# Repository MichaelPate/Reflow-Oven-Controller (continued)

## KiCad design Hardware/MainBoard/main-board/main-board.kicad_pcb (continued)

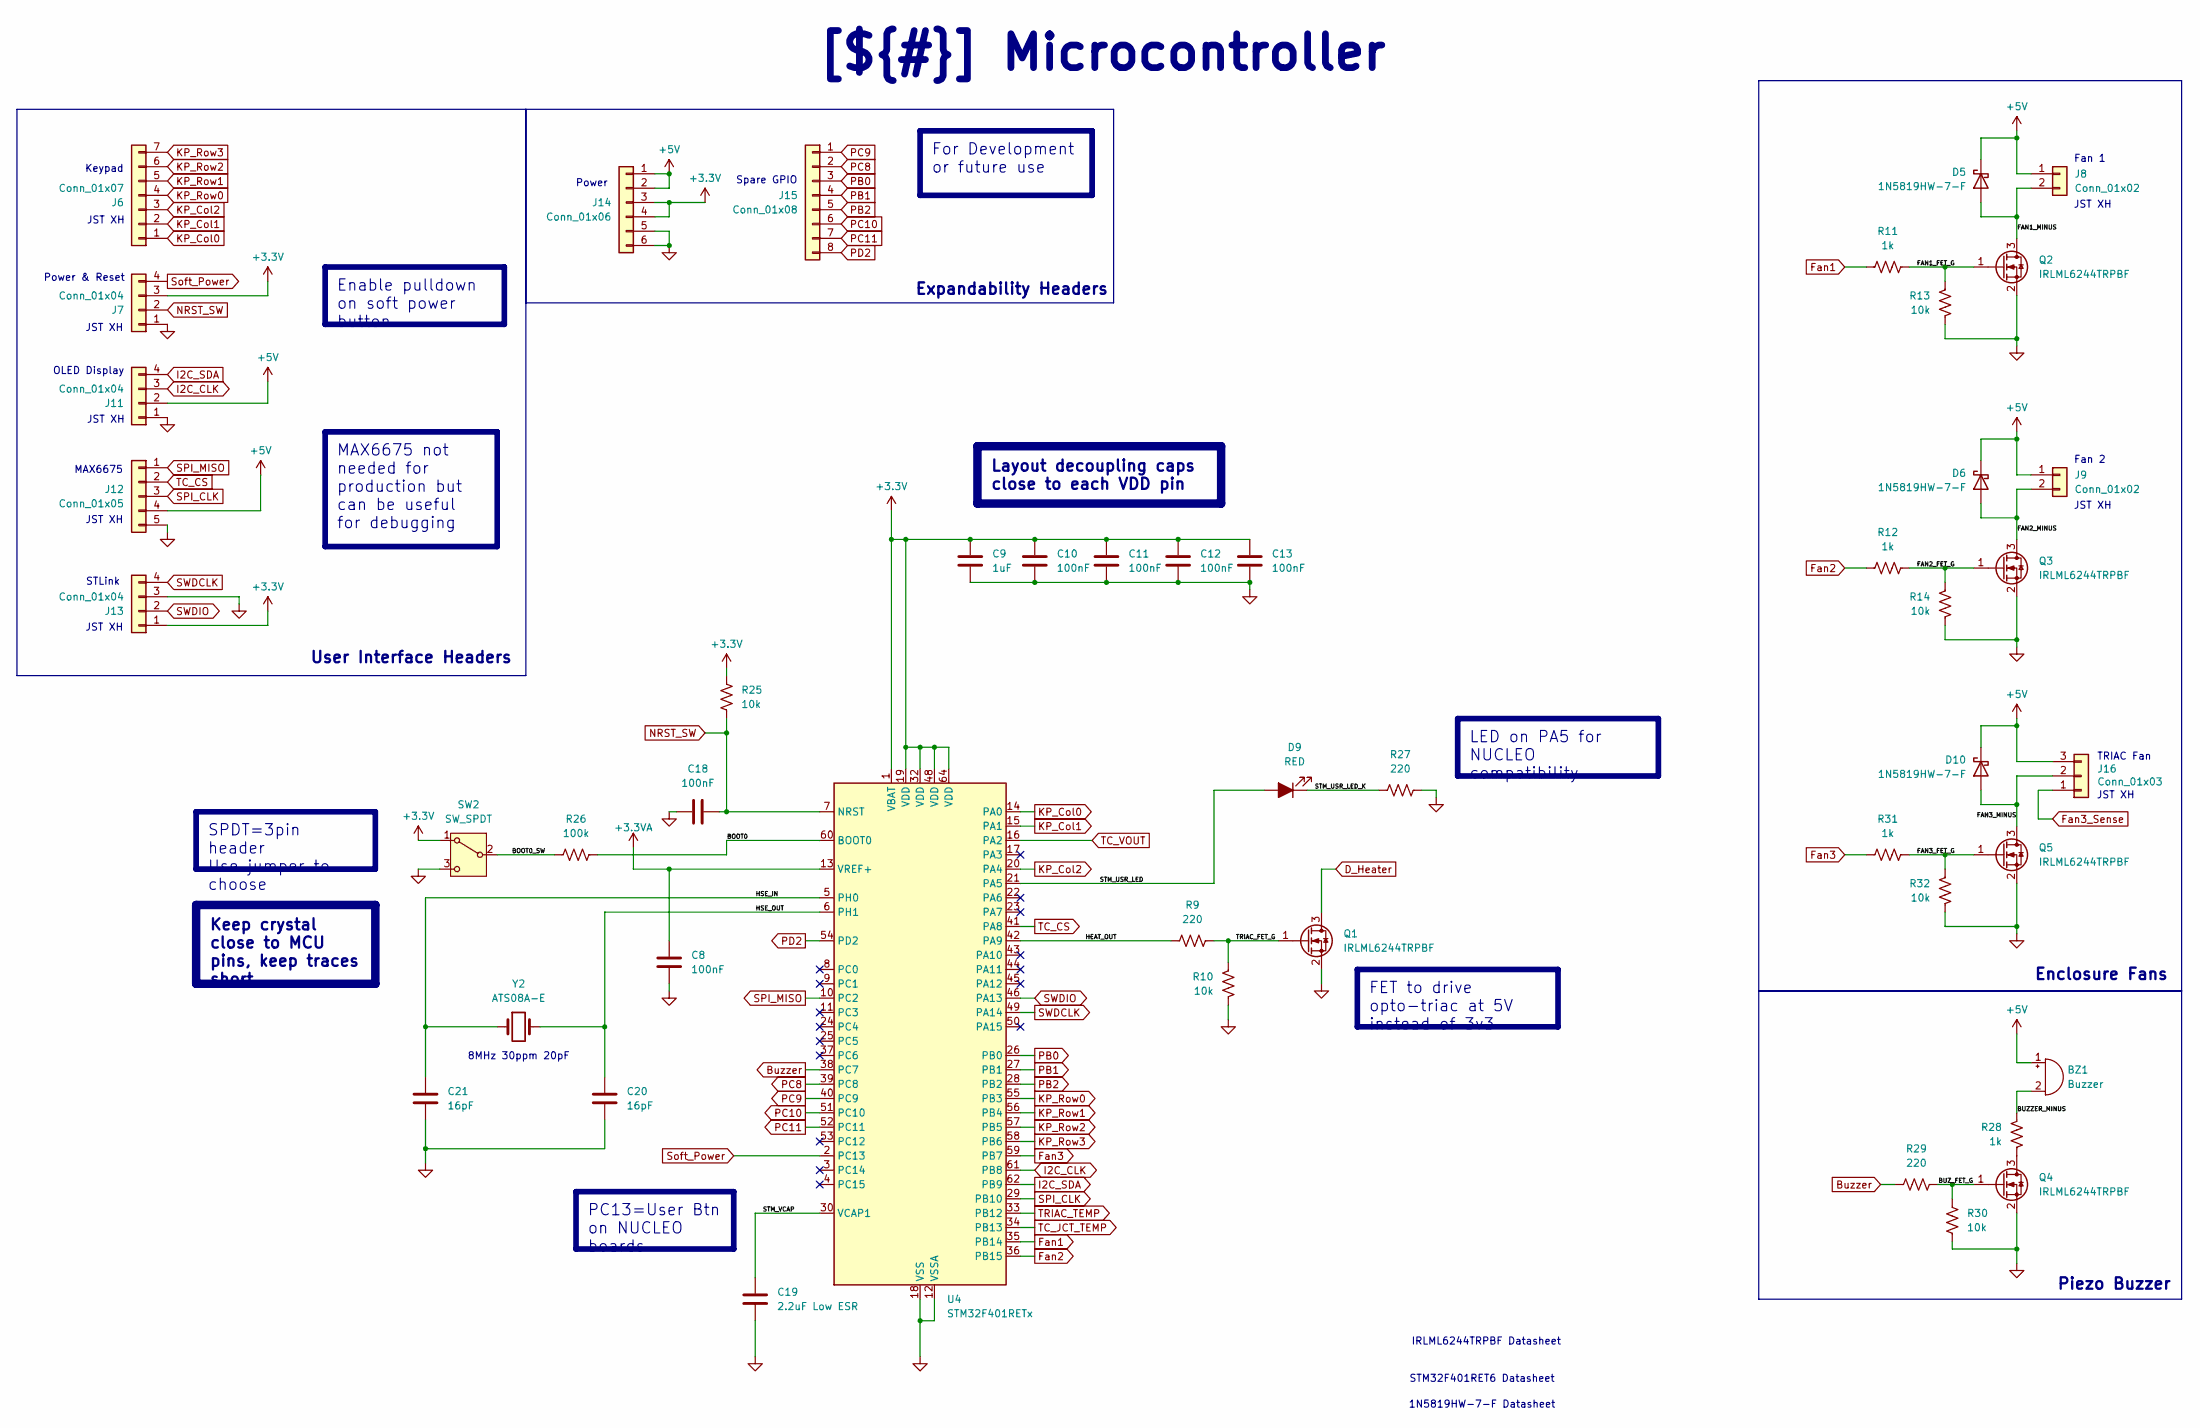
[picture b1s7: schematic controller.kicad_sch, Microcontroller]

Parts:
BZ1: Buzzer; Buzzer_12x9.5RM7.6
C8, C10, C11, C12, C13, C18: 100nF; C_0603_1608Metric_Pad1.08x0.95mm_HandSolder
C9: 1uF; C_0805_2012Metric_Pad1.18x1.45mm_HandSolder
C19: 2.2uF Low ESR; C_0805_2012Metric_Pad1.18x1.45mm_HandSolder
C20, C21: 16pF; C_0402_1005Metric_Pad0.74x0.62mm_HandSolder
D5, D6, D10: 1N5819HW-7-F; D_SOD-123
D9: RED; LED_0603_1608Metric_Pad1.05x0.95mm_HandSolder
J6: Conn_01x07; JST_XH_B7B-XH-A_1x07_P2.50mm_Vertical
J7, J11, J13: Conn_01x04; JST_XH_B4B-XH-A_1x04_P2.50mm_Vertical
J8, J9: Conn_01x02; JST_XH_B2B-XH-A_1x02_P2.50mm_Vertical
J12: Conn_01x05; JST_XH_B5B-XH-A_1x05_P2.50mm_Vertical
J14: Conn_01x06; PinHeader_1x06_P2.54mm_Vertical
J15: Conn_01x08; PinHeader_1x08_P2.54mm_Vertical
J16: Conn_01x03; JST_XH_B3B-XH-A_1x03_P2.50mm_Vertical
Q1, Q2, Q3, Q4, Q5: IRLML6244TRPBF; SOT-23
R9, R27, R29: 220; R_0603_1608Metric_Pad0.98x0.95mm_HandSolder
R10, R13, R14, R25, R30, R32: 10k; R_0603_1608Metric_Pad0.98x0.95mm_HandSolder
R11, R12, R28, R31: 1k; R_0603_1608Metric_Pad0.98x0.95mm_HandSolder
R26: 100k; R_0603_1608Metric_Pad0.98x0.95mm_HandSolder
SW2: SW_SPDT; PinHeader_1x03_P2.54mm_Vertical
U4: STM32F401RETx; LQFP-64_10x10mm_P0.5mm
Y2: ATS08A-E; Crystal_HC49-4H_Vertical

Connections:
+3.3V: C9.1, C10.1, C11.1, C12.1, C13.1, J7.3, J13.1, J14.3, J14.4, R25.1, SW2.1 (A), U4.1 (VBAT), U4.19 (VDD), U4.32 (VDD), U4.48 (VDD), U4.64 (VDD); also elsewhere on the board
+3.3VA: C8.1, U4.13 (VREF+); also elsewhere on the board
+5V: BZ1.1 (+), D5.1 (K), D6.1 (K), D10.1 (K), J8.1, J9.1, J11.2, J12.4, J14.1, J14.2, J16.3; also elsewhere on the board
/Block Diagram/MCU Page 5/BOOT0: R26.2, U4.60 (BOOT0)
/Block Diagram/MCU Page 5/BOOT0_SW: R26.1, SW2.2 (B)
/Block Diagram/MCU Page 5/BUZZER_MINUS: BZ1.2 (-), R28.1
/Block Diagram/MCU Page 5/BUZ_FET_G: Q4.1 (G), R29.2, R30.1
/Block Diagram/MCU Page 5/FAN1_FET_G: Q2.1 (G), R11.2, R13.1
/Block Diagram/MCU Page 5/FAN1_MINUS: D5.2 (A), J8.2, Q2.3 (D)
/Block Diagram/MCU Page 5/FAN2_FET_G: Q3.1 (G), R12.2, R14.1
/Block Diagram/MCU Page 5/FAN2_MINUS: D6.2 (A), J9.2, Q3.3 (D)
/Block Diagram/MCU Page 5/FAN3_FET_G: Q5.1 (G), R31.2, R32.1
/Block Diagram/MCU Page 5/FAN3_MINUS: D10.2 (A), J16.2, Q5.3 (D)
/Block Diagram/MCU Page 5/HEAT_OUT: R9.1, U4.42 (PA9)
/Block Diagram/MCU Page 5/HSE_IN: C21.1, U4.5 (PH0), Y2.1
/Block Diagram/MCU Page 5/HSE_OUT: C20.1, U4.6 (PH1), Y2.2
/Block Diagram/MCU Page 5/STM_USR_LED: D9.2 (A), U4.21 (PA5)
/Block Diagram/MCU Page 5/STM_USR_LED_K: D9.1 (K), R27.1
/Block Diagram/MCU Page 5/STM_VCAP: C19.1, U4.30 (VCAP1)
/Block Diagram/MCU Page 5/TRIAC_FET_G: Q1.1 (G), R9.2, R10.1
Buzzer: R29.1, U4.38 (PC7)
D_Heater: Q1.3 (D); also elsewhere on the board
Fan1: R11.1, U4.35 (PB14)
Fan2: R12.1, U4.36 (PB15)
Fan3: R31.1, U4.59 (PB7)
Fan3_Sense: J16.1
GND: C8.2, C9.2, C10.2, C11.2, C12.2, C13.2, C18.1, C19.2, C20.2, C21.2, J7.1, J11.1, J12.5, J13.3, J14.5, J14.6, Q1.2 (S), Q2.2 (S), Q3.2 (S), Q4.2 (S), Q5.2 (S), R10.2, R13.2, R14.2, R27.2, R30.2, R32.2, SW2.3 (C), U4.12 (VSSA), U4.18 (VSS), U4.31 (VSS), U4.47 (VSS), U4.63 (VSS); also elsewhere on the board
I2C_CLK: J11.3, U4.61 (PB8)
I2C_SDA: J11.4, U4.62 (PB9)
KP_Col0: J6.1, U4.14 (PA0)
KP_Col1: J6.2, U4.15 (PA1)
KP_Col2: J6.3, U4.20 (PA4)
KP_Row0: J6.4, U4.55 (PB3)
KP_Row1: J6.5, U4.56 (PB4)
KP_Row2: J6.6, U4.57 (PB5)
KP_Row3: J6.7, U4.58 (PB6)
NRST_SW: C18.2, J7.2, R25.2, U4.7 (NRST)
unnamed: Q4.3 (D), R28.2
PB0: J15.3, U4.26 (PB0)
PB1: J15.4, U4.27 (PB1)
PB2: J15.5, U4.28 (PB2)
PC8: J15.2, U4.39 (PC8)
PC9: J15.1, U4.40 (PC9)
PC10: J15.6, U4.51 (PC10)
PC11: J15.7, U4.52 (PC11)
PD2: J15.8, U4.54 (PD2)
SPI_CLK: J12.3, U4.29 (PB10)
SPI_MISO: J12.1, U4.10 (PC2)
SWDCLK: J13.4, U4.49 (PA14)
SWDIO: J13.2, U4.46 (PA13)
Soft_Power: J7.4, U4.2 (PC13)
TC_CS: J12.2, U4.41 (PA8)
TC_JCT_TEMP: U4.34 (PB13); also elsewhere on the board
TC_VOUT: U4.16 (PA2); also elsewhere on the board
TRIAC_TEMP: U4.33 (PB12); also elsewhere on the board

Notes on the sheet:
User Interface Headers
Piezo Buzzer
Enclosure Fans
Keypad
JST XH
8MHz 30ppm 20pF
Spare GPIO
TRIAC Fan
STM32F401RET6 Datasheet
1N5819HW-7-F Datasheet
MAX6675
Expandability Headers
Fan 1
Power
Power & Reset
OLED Display
STLink
IRLML6244TRPBF Datasheet
Fan 2
SPDT=3pin header Use jumper to choose
LED on PA5 for NUCLEO compatibility
MAX6675 not needed for production but can be useful for debugging
PC13=User Btn on NUCLEO boards
[${#}] ${TITLE}
Layout decoupling caps close to each VDD pin
For Development or future use
Keep crystal close to MCU pins, keep traces short
Enable pulldown on soft power button
FET to drive opto-triac at 5V instead of 3v3

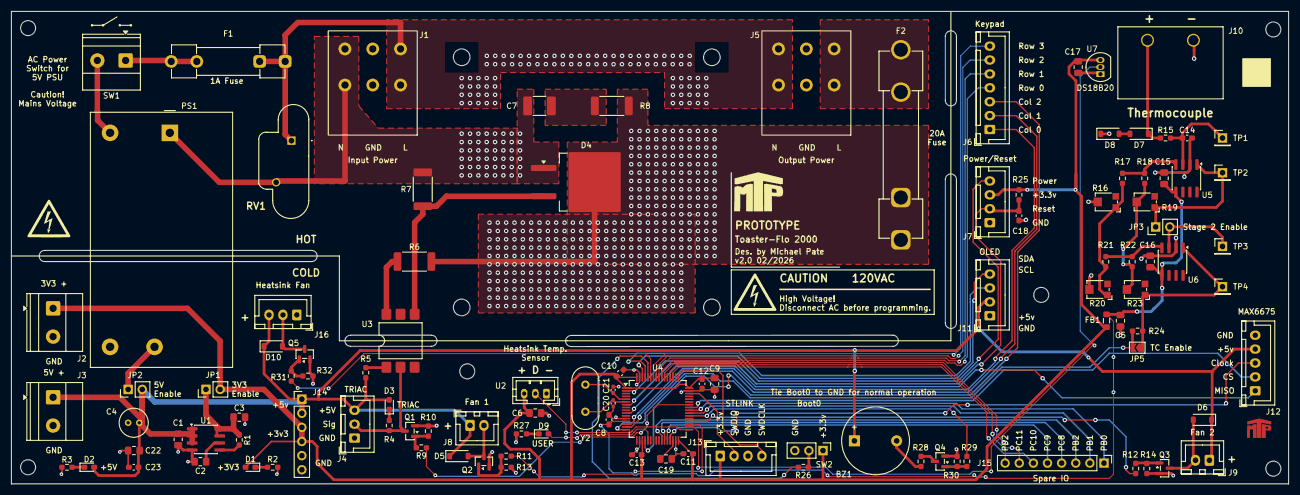
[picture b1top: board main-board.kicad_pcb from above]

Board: 4 copper layers, 229.8 x 85.0 mm, 122 parts (0 on the bottom side), 84 nets.

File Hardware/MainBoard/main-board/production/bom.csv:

Designator,Footprint,Quantity,Value,LCSC Part #
BZ1,Buzzer_12x9.5RM7.6,1,Buzzer,
"C1, C3, C5",0805,3,10uF,
"C10, C11, C12, C13, C18, C23, C8",0603,7,100nF,
C14,0603,1,104,
"C15, C16",0805,2,100nF,
"C17, C2, C22, C6, C9",0805,5,1uF,
C19,0805,1,2.2uF Low ESR,
"C20, C21",0402,2,16pF,
C4,C_Radial_D5.0mm_H5.0mm_P2.00mm,1,47uF,
C7,1812,1,10nF 250V,
"D1, D2, D3, D9",0603,4,RED,
"D10, D5, D6",D_SOD-123,3,1N5819HW-7-F,
D4,TO-263-2,1,T2035T-8G-RT,
"D7, D8",D_SOD-123,2,BZT52C4V7-13-F,
F1,Fuseholder_Clip-5x20mm_Littelfuse_100_Inline_P20.50x4.60mm_D1.30mm_Horizontal,1,1A,
F2,Fuseholder_Clip-6.3x32mm_Littelfuse_122_Inline_P34.21x7.62mm_D2.54mm_Horizontal,1,20A,
FB1,0805,1,WLBD2012HCU601TH,
"J1, J5",SPTA-THR 2.53-5.0 P26,2,1366005,
J10,CONN_4DB-P108-02_TEC,1,4DB-P108-02,
"J11, J13, J7",JST_XH_B4B-XH-A_1x04_P2.50mm_Vertical,3,Conn_01x04,
J12,JST_XH_B5B-XH-A_1x05_P2.50mm_Vertical,1,Conn_01x05,
J14,PinHeader_1x06_P2.54mm_Vertical,1,Conn_01x06,
J15,PinHeader_1x08_P2.54mm_Vertical,1,Conn_01x08,
"J16, J4",JST_XH_B3B-XH-A_1x03_P2.50mm_Vertical,2,Conn_01x03,
"J2, J3","TerminalBlock_Phoenix_MKDS-1,5-2-5.08_1x02_P5.08mm_Horizontal",2,Conn_01x02,
J6,JST_XH_B7B-XH-A_1x07_P2.50mm_Vertical,1,Conn_01x07,
"J8, J9",JST_XH_B2B-XH-A_1x02_P2.50mm_Vertical,2,Conn_01x02,
"JP1, JP2, JP3",PinHeader_1x02_P2.54mm_Vertical,3,Jumper_2_Open,
JP5,SolderJumper-2_P1.3mm_Open_TrianglePad1.0x1.5mm,1,Jumper_2_Open,
PS1,Converter_ACDC_MeanWell_IRM-10-xx_THT,1,IRM-10-5,
"Q1, Q2, Q3, Q4, Q5",SOT-23,5,IRLML6244TRPBF,
"R1, R10, R13, R14, R25, R30, R32",0603,7,10k,
"R11, R12, R15, R24, R28, R31",0603,6,1k,
"R16, R20",Potentiometer_Bourns_TC33X_Vertical,2,TC33X-2-103E,
"R17, R21",0603,2,15k,
"R18, R22",0603,2,560,
"R19, R23",Potentiometer_Bourns_TC33X_Vertical,2,TC33X-2-102E,
"R2, R27, R29, R9",0603,4,220,
R26,0603,1,100k,
"R3, R4, R5",0603,3,330,
"R6, R7",2512,2,330,
R8,2512,1,39,
RV1,TMOV20RP150E,1,TMOV20RP150E,
SW1,"TerminalBlock_Phoenix_MKDS-1,5-2-5.08_1x02_P5.08mm_Horizontal",1,SW_SPST,
SW2,PinHeader_1x03_P2.54mm_Vertical,1,SW_SPDT,
"TP1, TP2, TP3, TP4",PinHeader_1x01_P2.54mm_Vertical,4,TestPoint,
U1,SOIC-8_3.9x4.9mm_P1.27mm,1,MCP1727T-3302E/SN,
U2,JST_PH_B3B-PH-K_1x03_P2.00mm_Vertical,1,DS18B20+,
U3,SMDIP-6_W9.53mm,1,MOC3083S-TA1,
U4,LQFP-64_10x10mm_P0.5mm,1,STM32F401RETx,
"U5, U6",SOIC-8_3.9x4.9mm_P1.27mm,2,OPA333AIDCKT,
U7,TO-92_Inline,1,DS18B20+,
Y2,Crystal_HC49-4H_Vertical,1,ATS08A-E,

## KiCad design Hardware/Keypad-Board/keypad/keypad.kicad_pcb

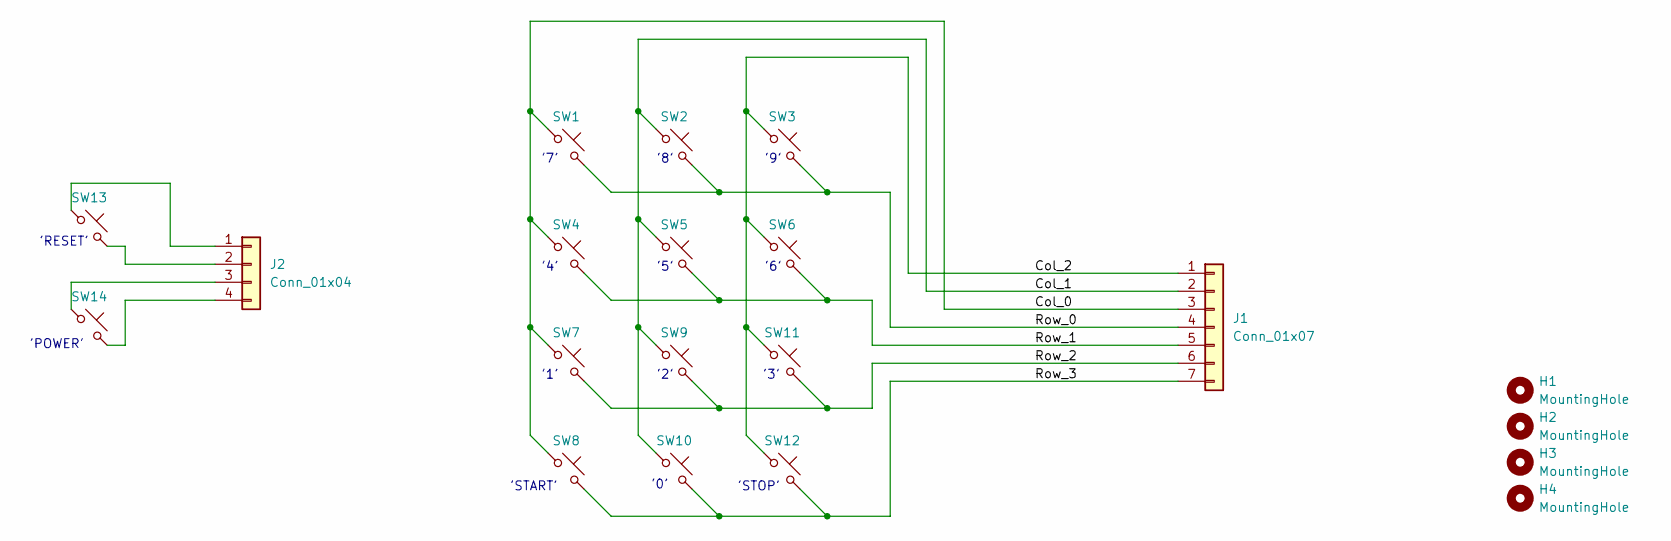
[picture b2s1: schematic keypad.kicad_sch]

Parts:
H1, H2, H3, H4: MountingHole; MountingHole_2.7mm_M2.5
J1: Conn_01x07; JST_XH_B7B-XH-A_1x07_P2.50mm_Vertical
J2: Conn_01x04; JST_XH_B4B-XH-A_1x04_P2.50mm_Vertical
SW1, SW2, SW3, SW4, SW5, SW6, SW7, SW8, SW9, SW10, SW11, SW12, SW13, SW14: SW_Push_45deg; SW_Cherry_MX_1.00u_PCB

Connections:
/Col_0: J1.3, SW1.1, SW4.1, SW7.1, SW8.1
/Col_1: J1.2, SW2.1, SW5.1, SW9.1, SW10.1
/Col_2: J1.1, SW3.1, SW6.1, SW11.1, SW12.1
/Row_0: J1.4, SW1.2, SW2.2, SW3.2
/Row_1: J1.5, SW4.2, SW5.2, SW6.2
/Row_2: J1.6, SW7.2, SW9.2, SW11.2
/Row_3: J1.7, SW8.2, SW10.2, SW12.2
unnamed: J2.1, SW13.1
unnamed: J2.2, SW13.2
unnamed: J2.3, SW14.1
unnamed: J2.4, SW14.2

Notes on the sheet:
'7'
'5'
'0'
'START'
'6'
'2'
'4'
'3'
'9'
'1'
'RESET'
'8'
'POWER'
'STOP'

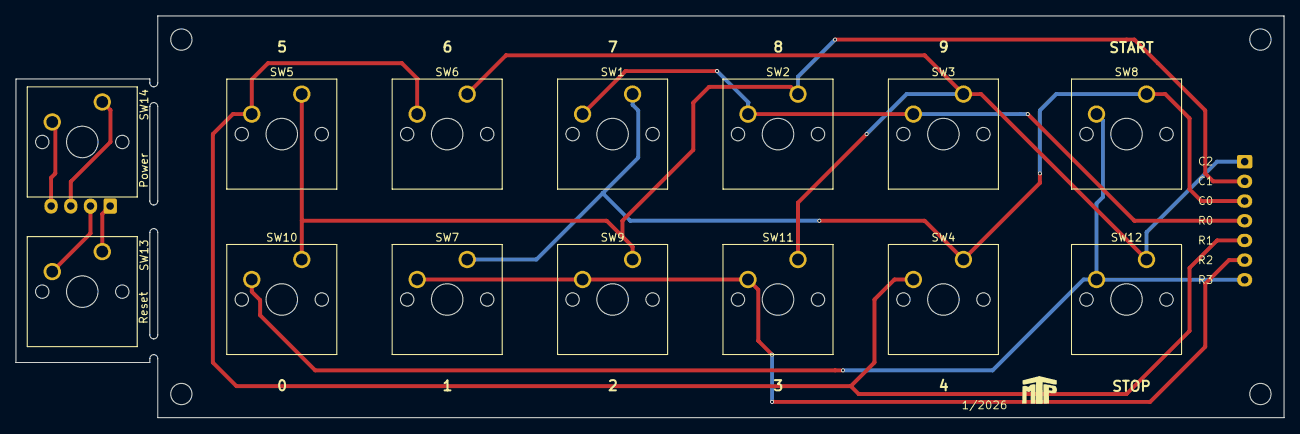
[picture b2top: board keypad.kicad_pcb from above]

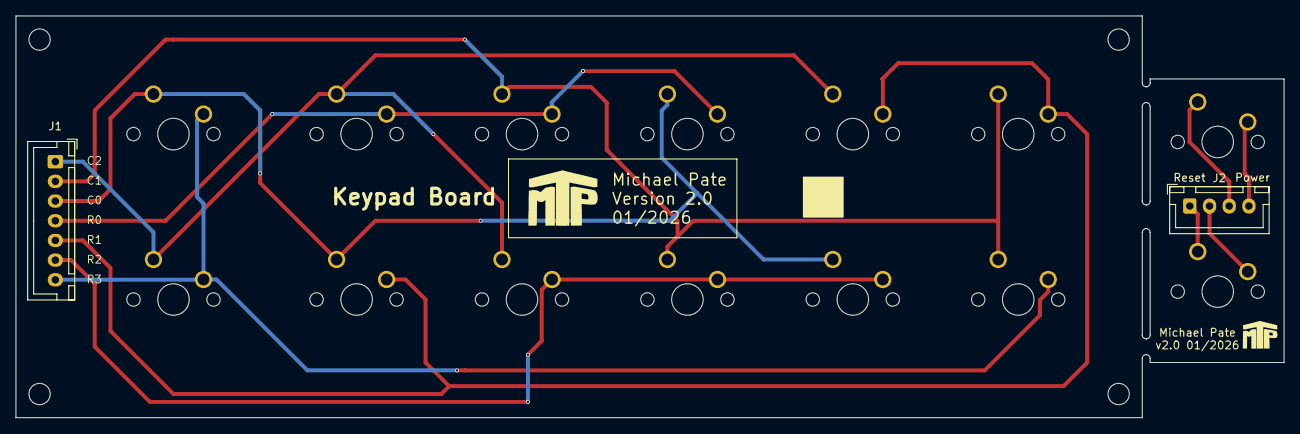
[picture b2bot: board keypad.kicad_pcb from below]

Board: 2 copper layers, 161.0 x 51.0 mm, 20 parts (2 on the bottom side), 11 nets.

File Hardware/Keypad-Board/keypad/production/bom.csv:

Designator,Footprint,Quantity,Value,LCSC Part #
J1,JST_XH_B7B-XH-A_1x07_P2.50mm_Vertical,1,Conn_01x07,
J2,JST_XH_B4B-XH-A_1x04_P2.50mm_Vertical,1,Conn_01x04,
"SW1, SW10, SW11, SW12, SW13, SW14, SW2, SW3, SW4, SW5, SW6, SW7, SW8, SW9",SW_Cherry_MX_1.00u_PCB,14,SW_Push_45deg,

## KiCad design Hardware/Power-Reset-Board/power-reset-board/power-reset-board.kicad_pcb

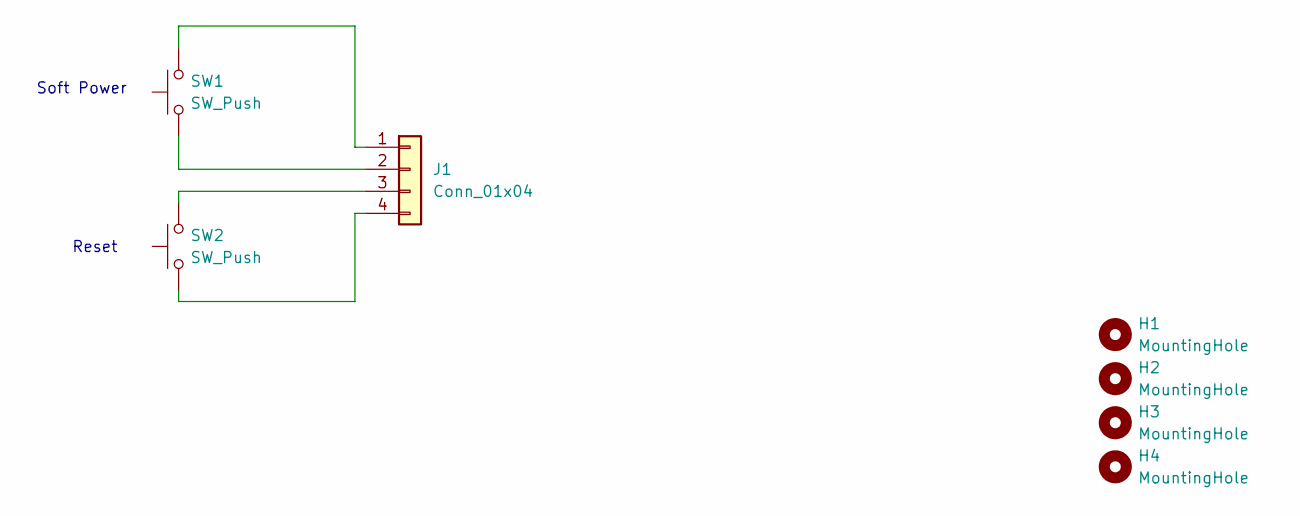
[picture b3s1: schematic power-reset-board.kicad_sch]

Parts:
H1, H2, H3, H4: MountingHole; MountingHole_2.7mm_M2.5
J1: Conn_01x04; JST_XH_B4B-XH-A_1x04_P2.50mm_Vertical
SW1, SW2: SW_Push; SW_Cherry_MX_1.00u_PCB

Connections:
unnamed: J1.1, SW1.2
unnamed: J1.2, SW1.1
unnamed: J1.3, SW2.2
unnamed: J1.4, SW2.1

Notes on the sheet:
Soft Power
Reset

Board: 2 copper layers, 7 parts (0 on the bottom side), 4 nets, no tracks yet.

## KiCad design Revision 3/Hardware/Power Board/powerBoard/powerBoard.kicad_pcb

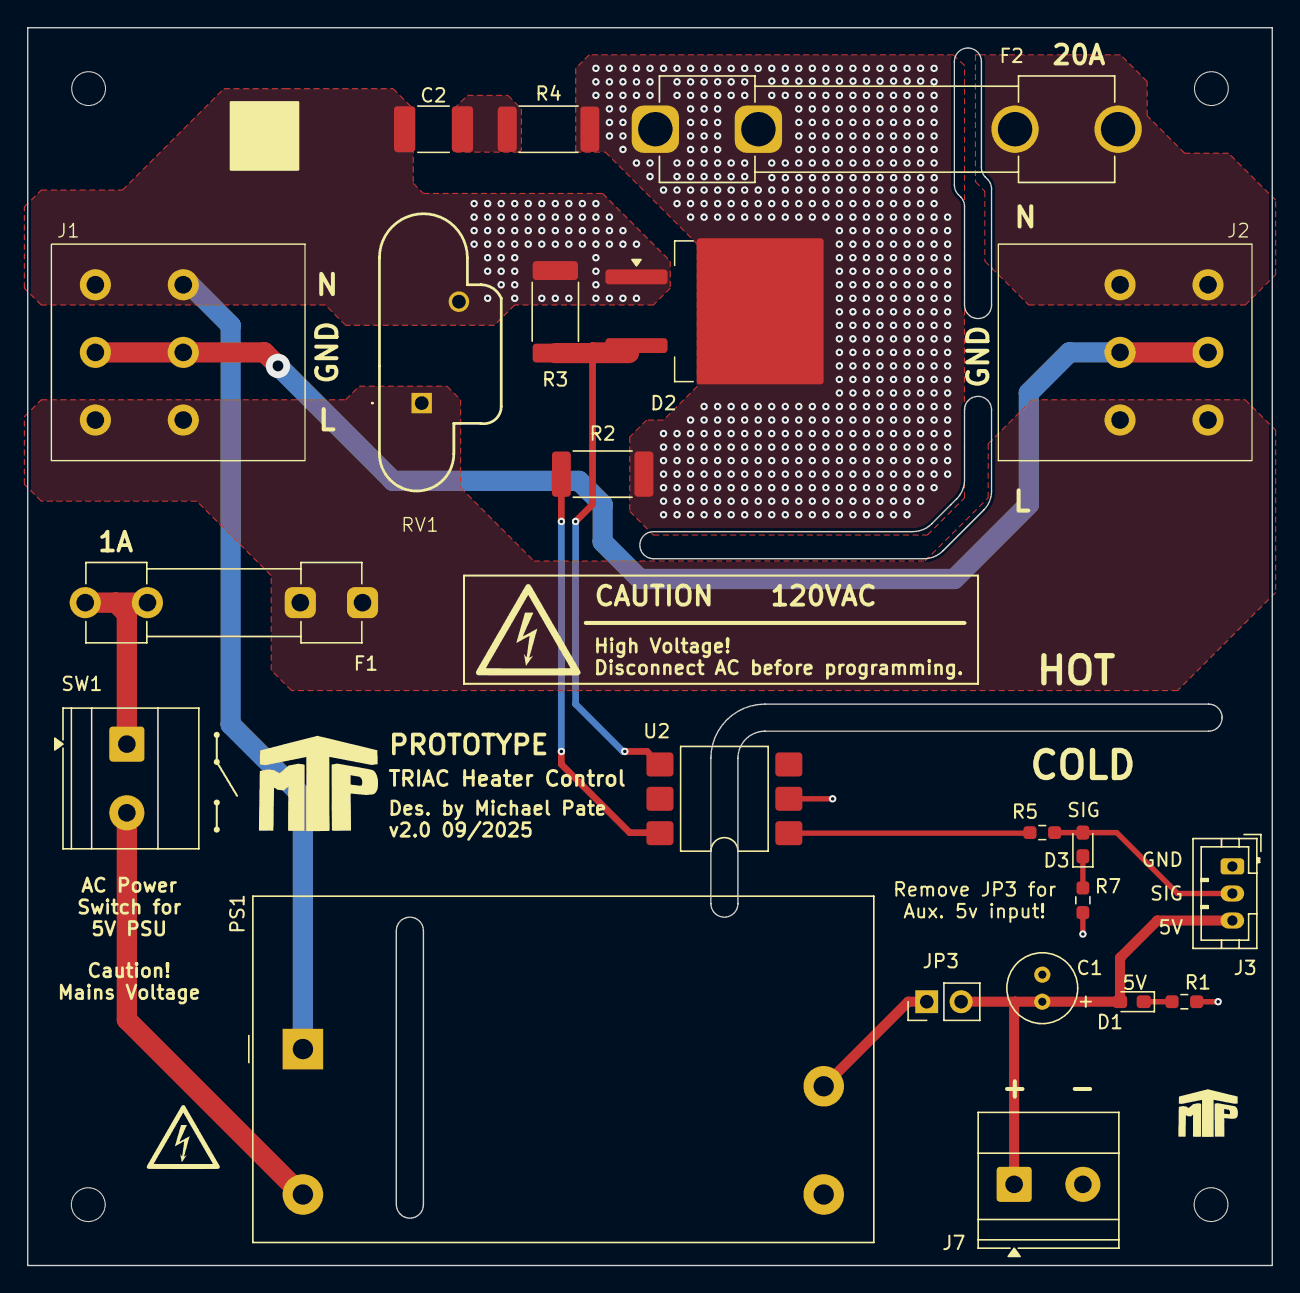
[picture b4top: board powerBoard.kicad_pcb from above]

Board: 2 copper layers, 92.0 x 91.5 mm, 26 parts (0 on the bottom side), 17 nets.

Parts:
C1: 100uF; C_Radial_D5.0mm_H5.0mm_P2.00mm
C2: 10nF 250V; C_1812_4532Metric_Pad1.57x3.40mm_HandSolder
D1, D3: RED; LED_0603_1608Metric_Pad1.05x0.95mm_HandSolder
D2: T2035T-8G-RT; TO-263-2
F1: 1A; Fuseholder_Clip-5x20mm_Littelfuse_100_Inline_P20.50x4.60mm_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
F2: 20A; Fuseholder_Clip-6.3x32mm_Littelfuse_122_Inline_P34.21x7.62m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
H1, H2, H3, H4: MountingHole_Pad; MountingHole_2.5mm
J1, J2: 1366005; SPTA-THR 2.53-5.0 P26
J3: Conn_01x03; JST_PH_B3B-PH-K_1x03_P2.00mm_Vertical
J7: Conn_01x02; TerminalBlock_Phoenix_MKDS-1,5-2-5.08_1x02_P5.08mm_Horizont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
JP3: Jumper_2_Open; PinHeader_1x02_P2.54mm_Vertical
PS1: IRM-10-5; Converter_ACDC_MeanWell_IRM-10-xx_THT
R1, R5, R7: 330; R_0603_1608Metric_Pad0.98x0.95mm_HandSolder
R2, R3: 330; R_2512_6332Metric_Pad1.40x3.35mm_HandSolder
R4: 39; R_2512_6332Metric_Pad1.40x3.35mm_HandSolder
RV1: TMOV20RP150E
SW1: SW_SPST; TerminalBlock_Phoenix_MKDS-1,5-2-5.08_1x02_P5.08mm_Horizont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
U2: MOC3083S-TA1; SMDIP-6_W9.53mm

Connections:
/Project Architecture/Heater Control/D3_K: D3.1 (K), R7.1
/Project Architecture/Heater Control/D_R5_OPTO: R5.2, U2.1
/Project Architecture/Heater Control/L1_F2: D2.2 (A2), F2.1, R2.2, R4.2
/Project Architecture/Heater Control/L1_F2_OPTO: R2.1, U2.6
/Project Architecture/Heater Control/L1_F2_RC: C2.1, R4.1
/Project Architecture/Heater Control/L1_HEATER: F2.2, J2.3
/Project Architecture/Heater Control/LN_OPTO: D2.3 (G), R3.2, U2.4
/Project Architecture/Power Supply/D1_K: D1.1 (K), R1.1
/Project Architecture/Power Supply/L1_F1: F1.2, SW1.1 (A)
/Project Architecture/Power Supply/L1_F1_SW: PS1.2 (AC/L), SW1.2 (B)
/Project Architecture/Power Supply/VDD_AC_DC: JP3.1 (A), PS1.4 (+Vo)
D_Heater: D3.2 (A), J3.2, R5.1
GND: C1.2, J3.1, J7.2, PS1.3 (-Vo), R1.2, R7.2, U2.2
GNDPWR: J1.2, J2.2
L1: F1.1, J1.3, J2.1, RV1.1
LN: C2.2, D2.1 (A1), J1.1, PS1.1 (AC/N), R3.1, RV1.2
VDD: C1.1, D1.2 (A), J3.3, J7.1, JP3.2 (B)

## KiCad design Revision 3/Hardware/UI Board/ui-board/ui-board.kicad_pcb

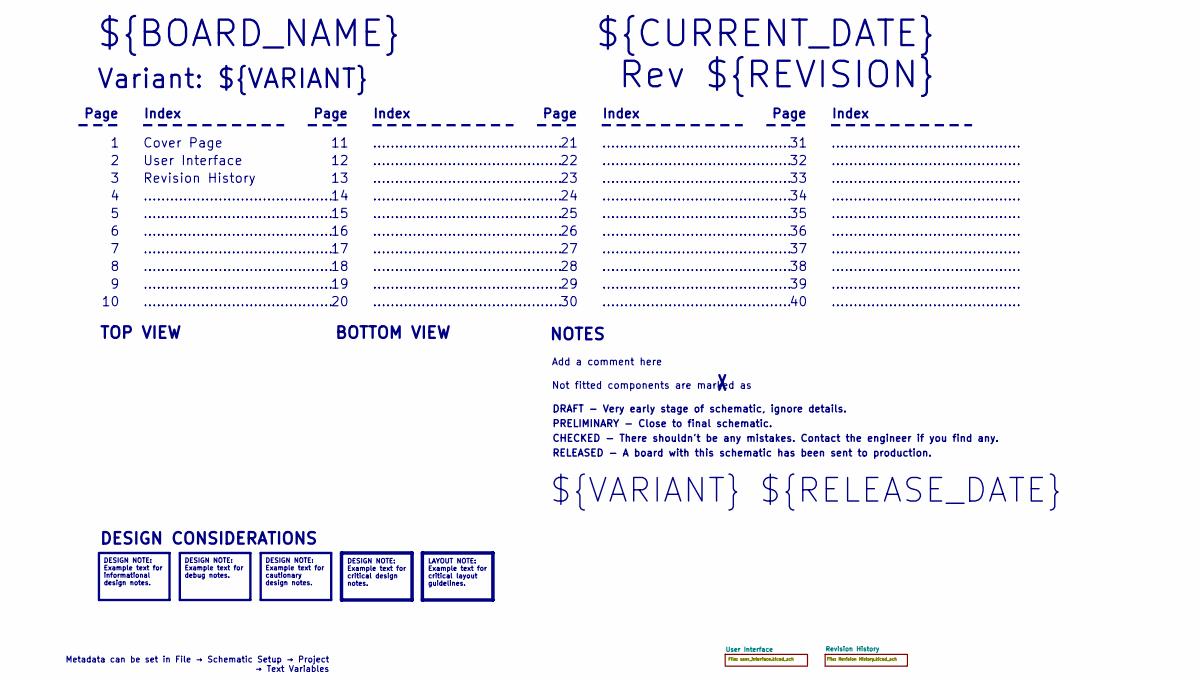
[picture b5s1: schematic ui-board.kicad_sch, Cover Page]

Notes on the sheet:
BOTTOM VIEW
...........................................
RELEASED - A board with this schematic has been sent to production.
Page
TOP VIEW
Not fitted components are marked as
Index
PRELIMINARY - Close to final schematic.
${VARIANT} ${RELEASE_DATE}
${CURRENT_DATE}
Variant: ${VARIANT}
Rev ${REVISION}
${BOARD_NAME}
DRAFT - Very early stage of schematic, ignore details.
User Interface
Add a comment here
Cover Page
NOTES
Revision History
CHECKED - There shouldn't be any mistakes. Contact the engineer if you find any.
DESIGN CONSIDERATIONS
Metadata can be set in File → Schematic Setup → Project → Text Variables
DESIGN NOTE: Example text for informational design notes.
LAYOUT NOTE: Example text for critical layout guidelines.
DESIGN NOTE: Example text for cautionary design notes.
DESIGN NOTE: Example text for debug notes.
DESIGN NOTE: Example text for critical design notes.

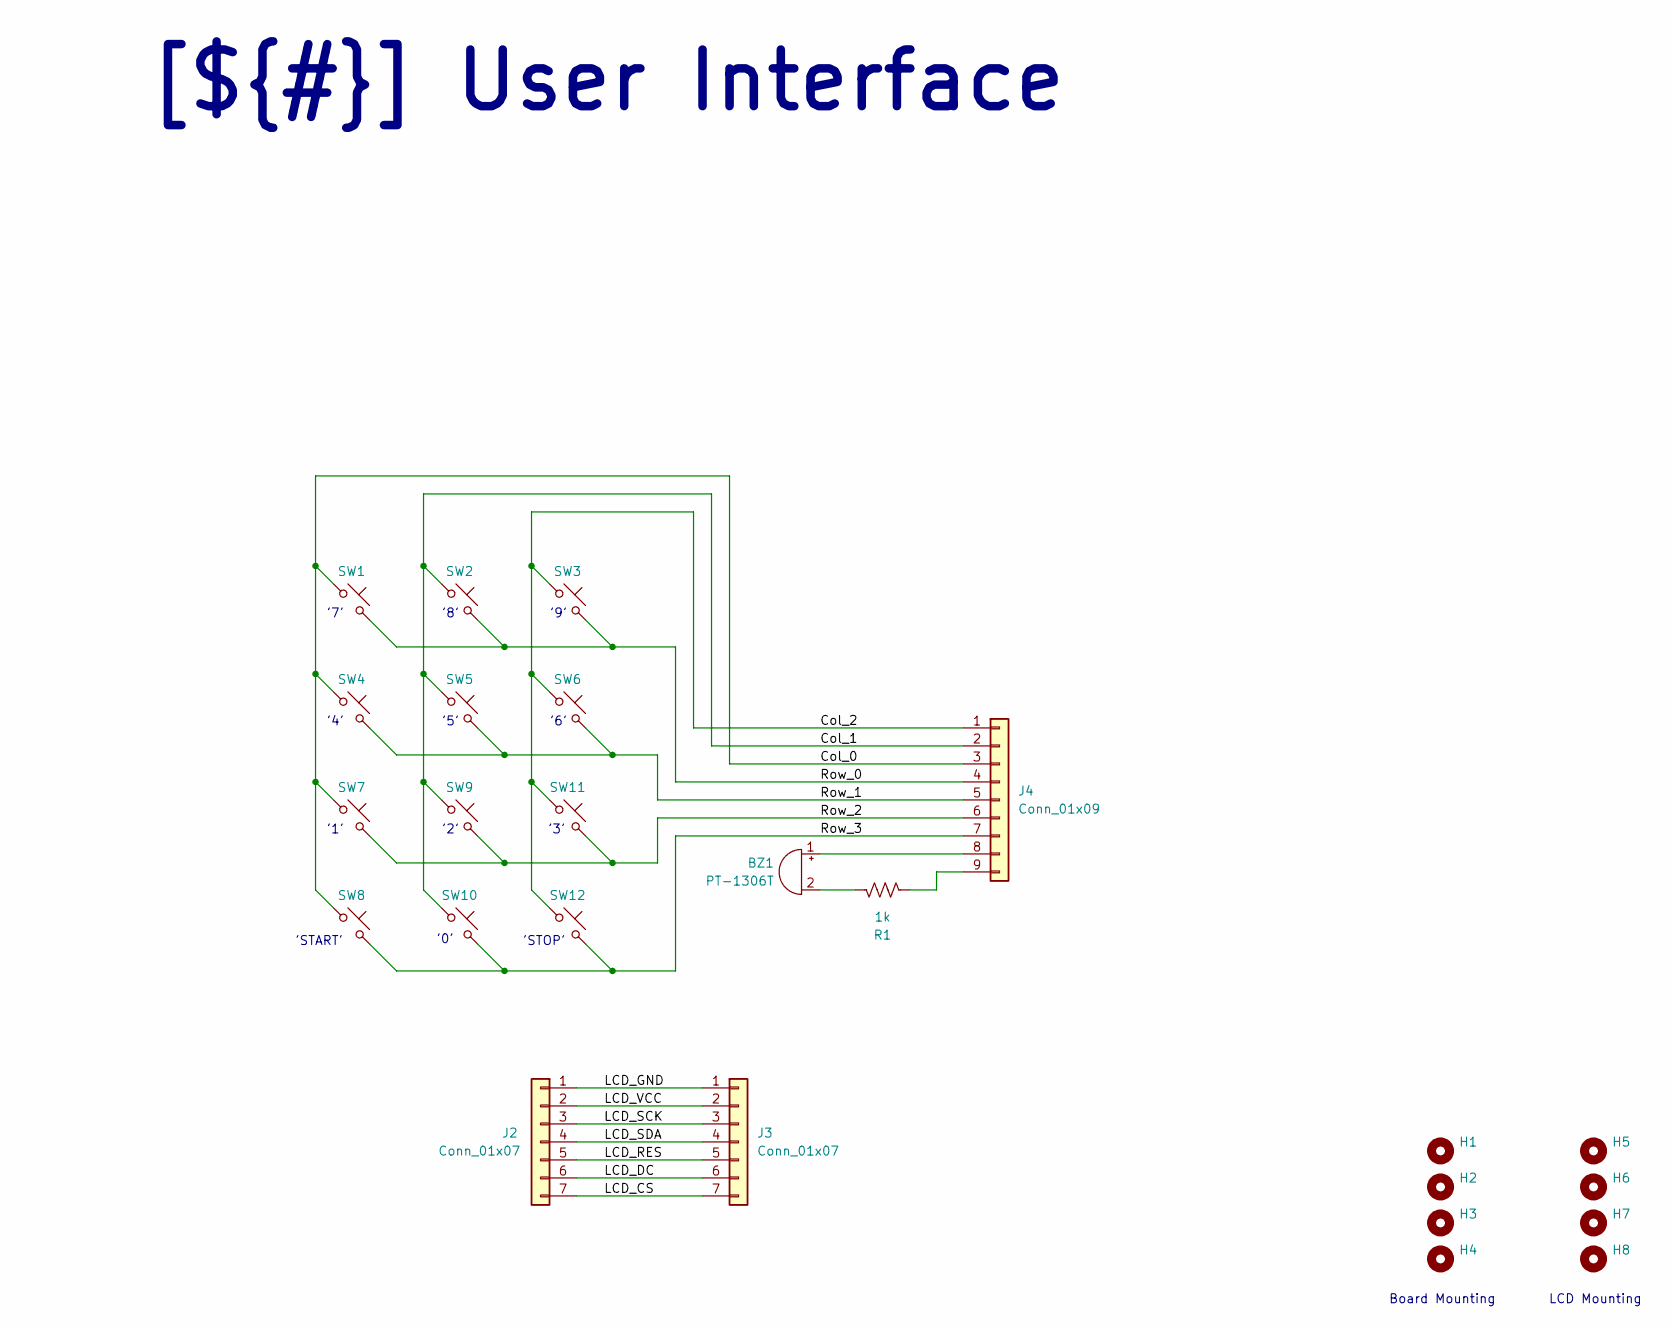
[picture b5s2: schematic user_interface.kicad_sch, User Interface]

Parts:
BZ1: PT-1306T; Buzzer_12x9.5RM7.6
H1, H2, H3, H4: MountingHole; MountingHole_3.2mm_M3
H5, H6, H7, H8: MountingHole; MountingHole_2.2mm_M2
J2: Conn_01x07; PinSocket_1x07_P2.54mm_Vertical
J3: Conn_01x07; PinHeader_1x07_P2.54mm_Vertical
J4: Conn_01x09; PinHeader_1x09_P2.54mm_Vertical
R1: 1k; R_0603_1608Metric_Pad0.98x0.95mm_HandSolder
SW1, SW2, SW3, SW4, SW5, SW6, SW7, SW8, SW9, SW10, SW11, SW12: SW_Push_45deg; SW_Cherry_MX_1.00u_PCB

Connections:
/User Interface/Col_0: J4.3, SW1.1, SW4.1, SW7.1, SW8.1
/User Interface/Col_1: J4.2, SW2.1, SW5.1, SW9.1, SW10.1
/User Interface/Col_2: J4.1, SW3.1, SW6.1, SW11.1, SW12.1
/User Interface/LCD_CS: J2.7, J3.7
/User Interface/LCD_DC: J2.6, J3.6
/User Interface/LCD_GND: J2.1, J3.1
/User Interface/LCD_RES: J2.5, J3.5
/User Interface/LCD_SCK: J2.3, J3.3
/User Interface/LCD_SDA: J2.4, J3.4
/User Interface/LCD_VCC: J2.2, J3.2
/User Interface/Row_0: J4.4, SW1.2, SW2.2, SW3.2
/User Interface/Row_1: J4.5, SW4.2, SW5.2, SW6.2
/User Interface/Row_2: J4.6, SW7.2, SW9.2, SW11.2
/User Interface/Row_3: J4.7, SW8.2, SW10.2, SW12.2
unnamed: BZ1.1 (+), J4.8
unnamed: BZ1.2 (-), R1.1
unnamed: J4.9, R1.2

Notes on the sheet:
'1'
'STOP'
LCD Mounting
'7'
'0'
Board Mounting
'3'
'START'
'6'
'2'
'9'
'8'
'4'
'5'
[${#}] ${TITLE}

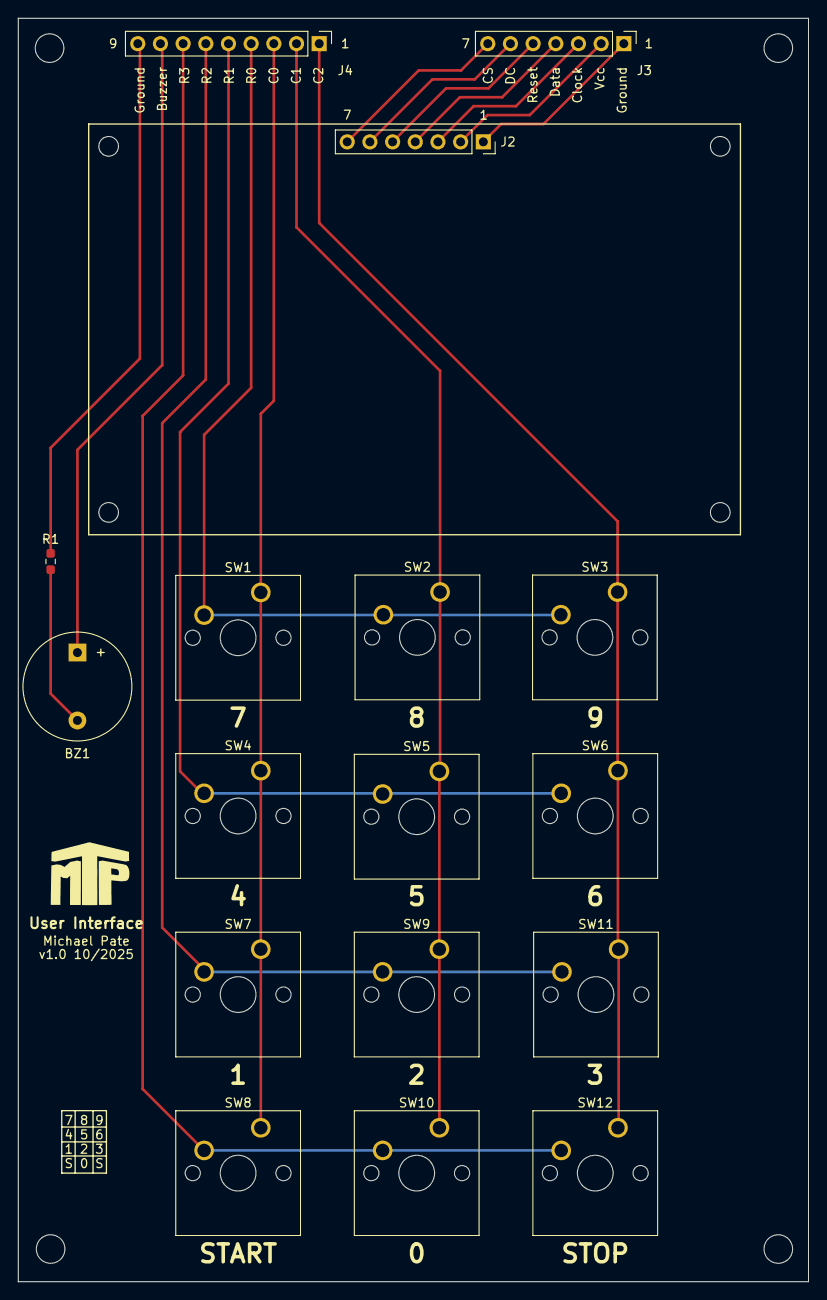
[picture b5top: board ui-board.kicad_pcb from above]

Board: 6 copper layers, 88.5 x 141.5 mm, 25 parts (0 on the bottom side), 17 nets.

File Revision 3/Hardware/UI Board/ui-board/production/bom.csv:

Designator,Footprint,Quantity,Value,LCSC Part #
BZ1,Buzzer_12x9.5RM7.6,1,PT-1306T,
J2,PinSocket_1x07_P2.54mm_Vertical,1,Conn_01x07,
J3,PinHeader_1x07_P2.54mm_Vertical,1,Conn_01x07,
J4,PinHeader_1x09_P2.54mm_Vertical,1,Conn_01x09,
R1,0603,1,1k,
"SW1, SW10, SW11, SW12, SW2, SW3, SW4, SW5, SW6, SW7, SW8, SW9",SW_Cherry_MX_1.00u_PCB,12,SW_Push_45deg,

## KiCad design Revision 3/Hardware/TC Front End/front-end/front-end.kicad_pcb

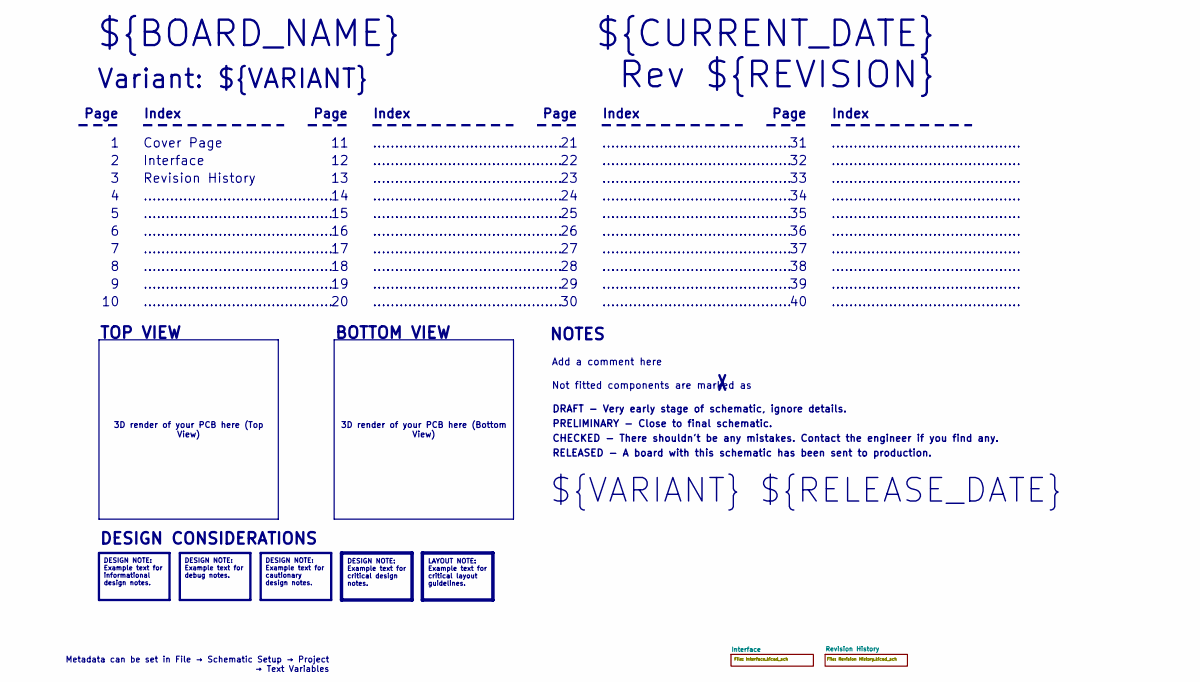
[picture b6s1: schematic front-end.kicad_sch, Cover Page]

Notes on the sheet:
BOTTOM VIEW
...........................................
RELEASED - A board with this schematic has been sent to production.
Page
TOP VIEW
Not fitted components are marked as
Index
PRELIMINARY - Close to final schematic.
${VARIANT} ${RELEASE_DATE}
${CURRENT_DATE}
Variant: ${VARIANT}
Rev ${REVISION}
${BOARD_NAME}
DRAFT - Very early stage of schematic, ignore details.
Interface
Add a comment here
Cover Page
NOTES
Revision History
CHECKED - There shouldn't be any mistakes. Contact the engineer if you find any.
DESIGN CONSIDERATIONS
3D render of your PCB here (Bottom View)
3D render of your PCB here (Top View)
Metadata can be set in File → Schematic Setup → Project → Text Variables
DESIGN NOTE: Example text for informational design notes.
LAYOUT NOTE: Example text for critical layout guidelines.
DESIGN NOTE: Example text for cautionary design notes.
DESIGN NOTE: Example text for debug notes.
DESIGN NOTE: Example text for critical design notes.
